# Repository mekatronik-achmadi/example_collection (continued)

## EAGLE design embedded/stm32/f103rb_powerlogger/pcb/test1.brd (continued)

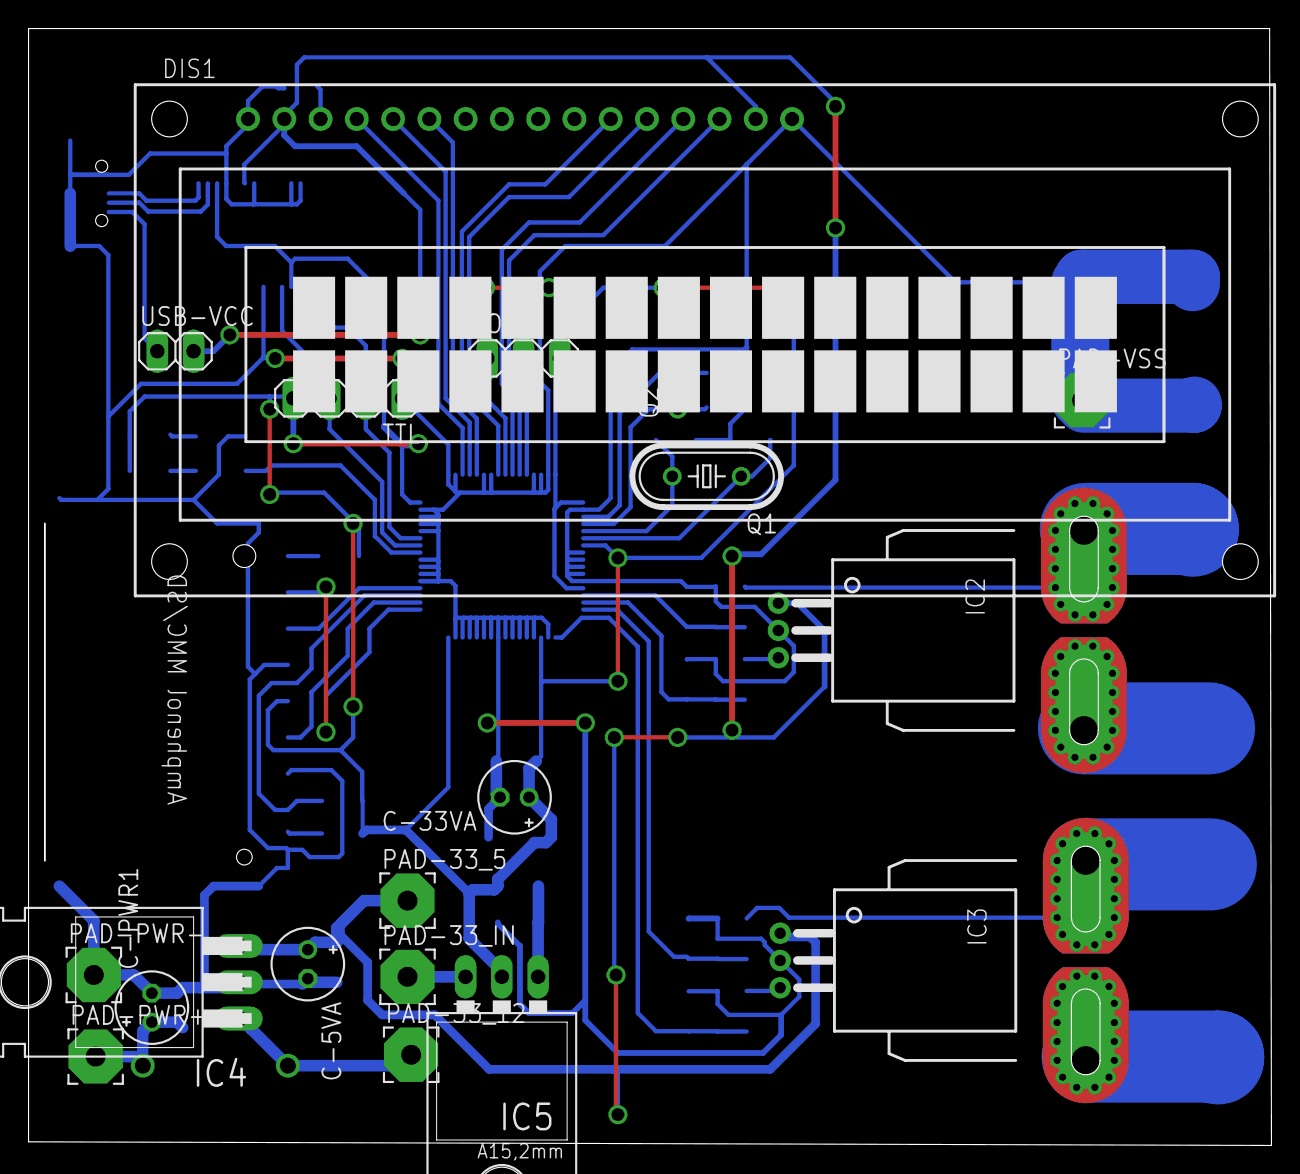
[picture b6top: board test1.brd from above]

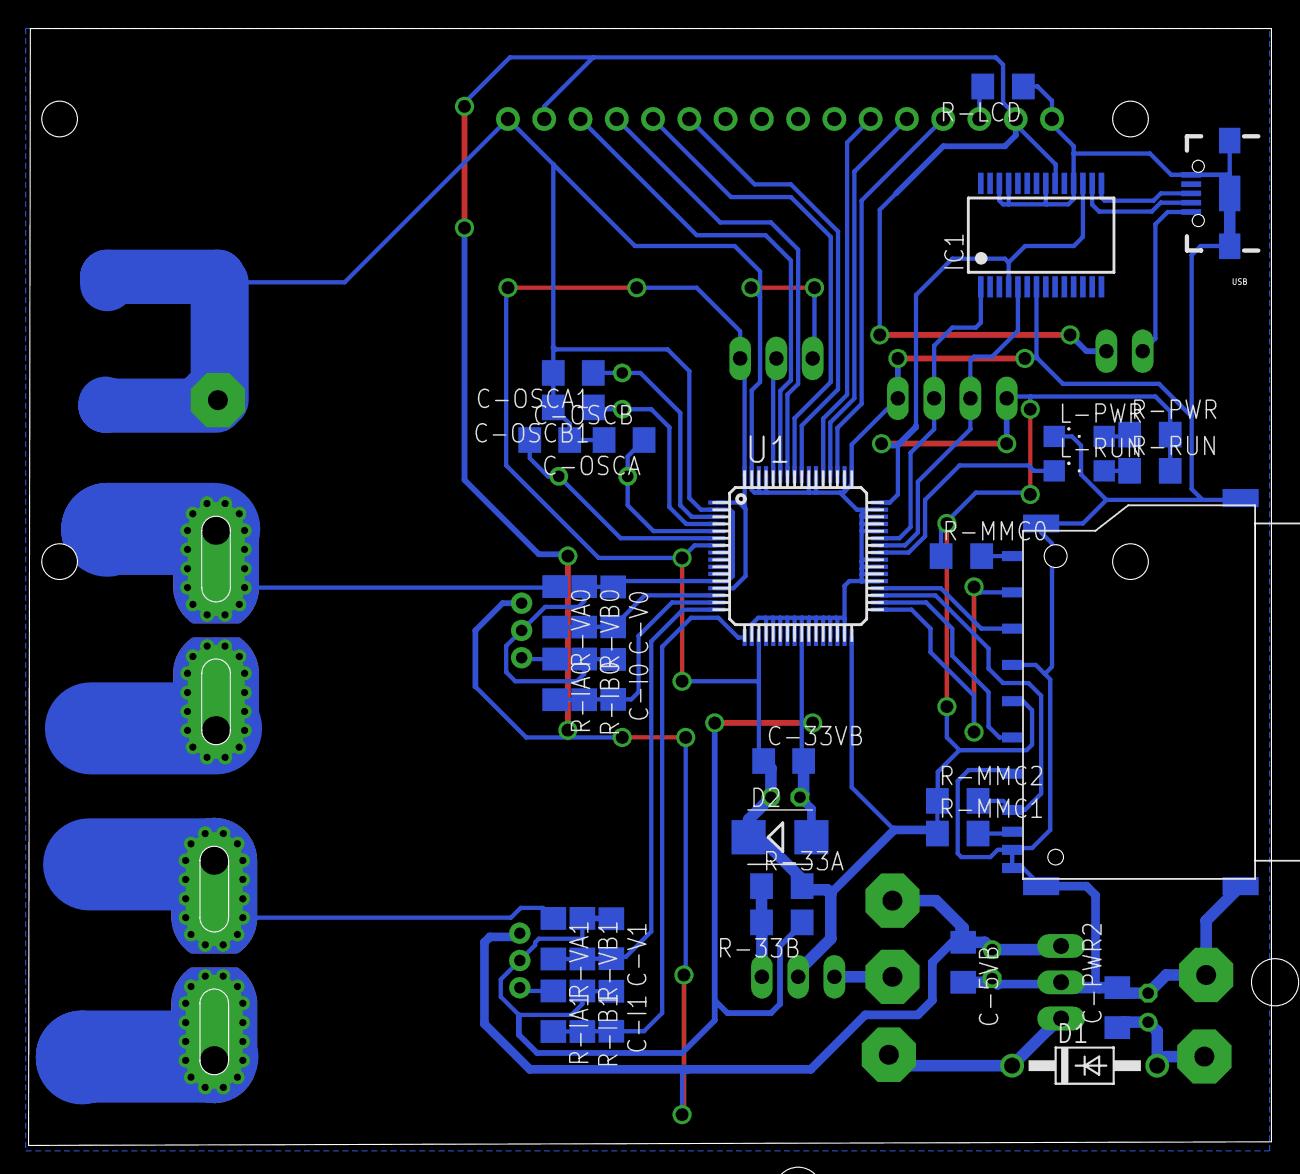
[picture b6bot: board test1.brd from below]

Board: 2 copper layers, 87.0 x 78.2 mm, 54 parts (35 on the bottom side), 42 nets.

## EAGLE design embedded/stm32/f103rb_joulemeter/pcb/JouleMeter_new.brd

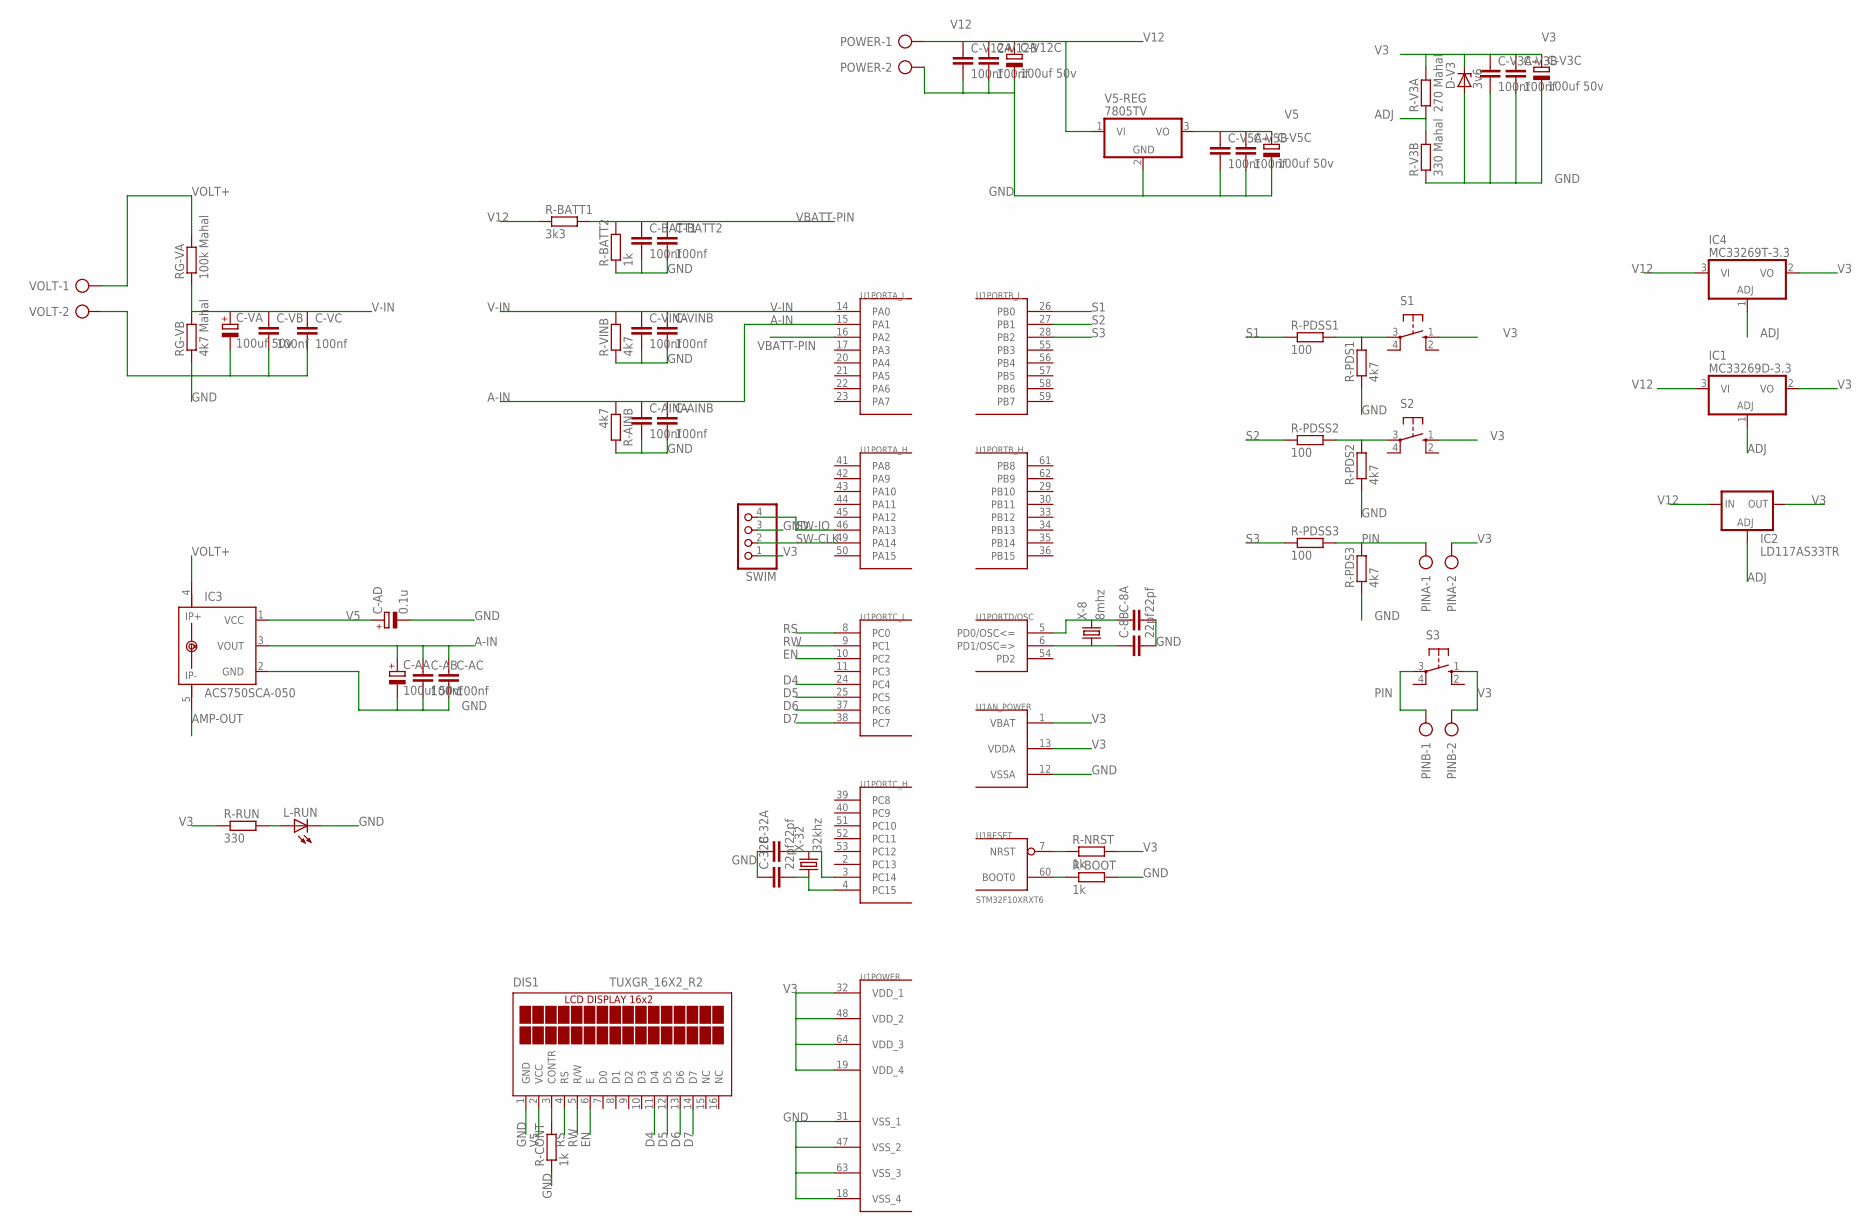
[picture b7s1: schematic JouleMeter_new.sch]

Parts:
C-8A, C-8B, C-32A, C-32B: 22pf; C025-024X044
C-AA: 100uf 50v; E2-5
C-AB: 100nf; C050-024X044
C-AC: 100nf; C050-024X044
C-AD: 0.1u; E2-5
C-AINA: 100nf; C050-024X044
C-AINB: 100nf; C050-024X044
C-BATT1, C-BATT2: 100nf; C050-024X044
C-V3A, C-V3B, C-V5A, C-V5B, C-V12A, C-V12B: 100nf; C050-024X044
C-V3C, C-V5C, C-V12C: 100uf 50v; E5-5
C-VA: 100uf 50v; E2-5
C-VB: 100nf; C050-024X044
C-VC: 100nf; C050-024X044
C-VINA: 100nf; C050-024X044
C-VINB: 100nf; C050-024X044
D-V3: 3v6; ZDIO-7.5
DIS1: TUXGR_16X2_R2
IC1: MC33269D-3.3; DPACK
IC2: LD117AS33TR; SOT223
IC3: ACS750SCA-050; ACS75050
IC4: MC33269T-3.3; TO220V
L-RUN: LED3MM
PINA: AK300/2
PINB: AK300/2
POWER: AK300/2
R-AINB: 4k7; 0204/7
R-BATT1: 3k3; 0204/7
R-BATT2: 1k; 0204/7
R-BOOT: 1k; 0204/7
R-CONT: 1k; 0204/7
R-NRST: 1k; 0204/7
R-PDS1, R-PDS2, R-PDS3: 4k7; 0204/7
R-PDSS1, R-PDSS2, R-PDSS3: 100; 0204/7
R-RUN: 330; 0204/7
R-V3A: 270 Mahal; 0204/7
R-V3B: 330 Mahal; 0204/7
R-VINB: 4k7; 0204/7
RG-VA: 100k Mahal; 0204/7
RG-VB: 4k7 Mahal; 0204/7
S1, S2: 10-XX; B3F-10XX
S3: 40-XX; B3F-40XX
SWIM: PINHD-1X4; 1X04
U1: STM32F10XRXT6; TQFP64
V5-REG: 7805TV; TO220V
VOLT: AK300/2
X-8: 8mhz; HC49U-V
X-32: 32khz; TC26V

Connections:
A-IN: C-AA.+, C-AB.1, C-AC.1, C-AINA.1, C-AINB.1, IC3.3 (VOUT), R-AINB.1, U1.15 (PA1)
ADJ: IC1.1 (ADJ), IC2.1 (ADJ), IC4.1 (ADJ), R-V3A.1, R-V3B.2
AMP-OUT: IC3.5 (IP-)
D4: DIS1.11 (D4), U1.24 (PC4)
D5: DIS1.12 (D5), U1.25 (PC5)
D6: DIS1.13 (D6), U1.37 (PC6)
D7: DIS1.14 (D7), U1.38 (PC7)
EN: DIS1.6 (E), U1.10 (PC2)
GND: C-8A.2, C-8B.2, C-32A.1, C-32B.1, C-AA.-, C-AB.2, C-AC.2, C-AD.-, C-AINA.2, C-AINB.2, C-BATT1.2, C-BATT2.2, C-V3A.2, C-V3B.2, C-V3C.-, C-V5A.2, C-V5B.2, C-V5C.-, C-V12A.2, C-V12B.2, C-V12C.-, C-VA.-, C-VB.2, C-VC.2, C-VINA.2, C-VINB.2, D-V3.A, DIS1.1 (GND), IC3.2 (GND), L-RUN.K (C), POWER.2, R-AINB.2, R-BATT2.1, R-BOOT.2, R-CONT.1, R-PDS1.1, R-PDS2.1, R-PDS3.1, R-V3B.1, R-VINB.1, RG-VB.1, SWIM.3, U1.12 (VSSA), U1.18 (VSS_4), U1.31 (VSS_1), U1.47 (VSS_2), U1.63 (VSS_3), V5-REG.2 (GND), VOLT.2
unnamed: R-PDS1.2, R-PDSS1.2, S1.3
unnamed: R-PDS2.2, R-PDSS2.2, S2.3
unnamed: DIS1.3 (CONTR), R-CONT.2
unnamed: C-32B.2, U1.4 (PC15), X-32.1
unnamed: C-32A.2, U1.3 (PC14), X-32.2
unnamed: C-8B.1, U1.6 (PD1/OSC=>), X-8.1
unnamed: C-8A.1, U1.5 (PD0/OSC<=), X-8.2
unnamed: R-NRST.1, U1.7 (NRST)
unnamed: R-BOOT.1, U1.60 (BOOT0)
unnamed: L-RUN.A, R-RUN.2
PIN: PINA.1, PINB.1, R-PDS3.2, R-PDSS3.2, S3.3
RS: DIS1.4 (RS), U1.8 (PC0)
RW: DIS1.5 (R/W), U1.9 (PC1)
S1: R-PDSS1.1, U1.26 (PB0)
S2: R-PDSS2.1, U1.27 (PB1)
S3: R-PDSS3.1, U1.28 (PB2)
SW-CLK: SWIM.2, U1.49 (PA14)
SW-IO: SWIM.4, U1.46 (PA13)
V3: C-V3A.1, C-V3B.1, C-V3C.+, D-V3.C, IC1.2 (VO), IC2.4 (OUT), IC4.2 (VO), PINA.2, PINB.2, R-NRST.2, R-RUN.1, R-V3A.2, S1.1 (S), S2.1 (S), S3.1 (S), SWIM.1, U1.1 (VBAT), U1.13 (VDDA), U1.19 (VDD_4), U1.32 (VDD_1), U1.48 (VDD_2), U1.64 (VDD_3)
V5: C-AD.+, C-V5A.1, C-V5B.1, C-V5C.+, DIS1.2 (VCC), IC3.1 (VCC), V5-REG.3 (VO)
V12: C-V12A.1, C-V12B.1, C-V12C.+, IC1.3 (VI), IC2.3 (IN), IC4.3 (VI), POWER.1, R-BATT1.1, V5-REG.1 (VI)
V-IN: C-VA.+, C-VB.1, C-VC.1, C-VINA.1, C-VINB.1, R-VINB.2, RG-VA.1, RG-VB.2, U1.14 (PA0)
VBATT-PIN: C-BATT1.1, C-BATT2.1, R-BATT1.2, R-BATT2.2, U1.16 (PA2)
VOLT+: IC3.4 (IP+), RG-VA.2, VOLT.1

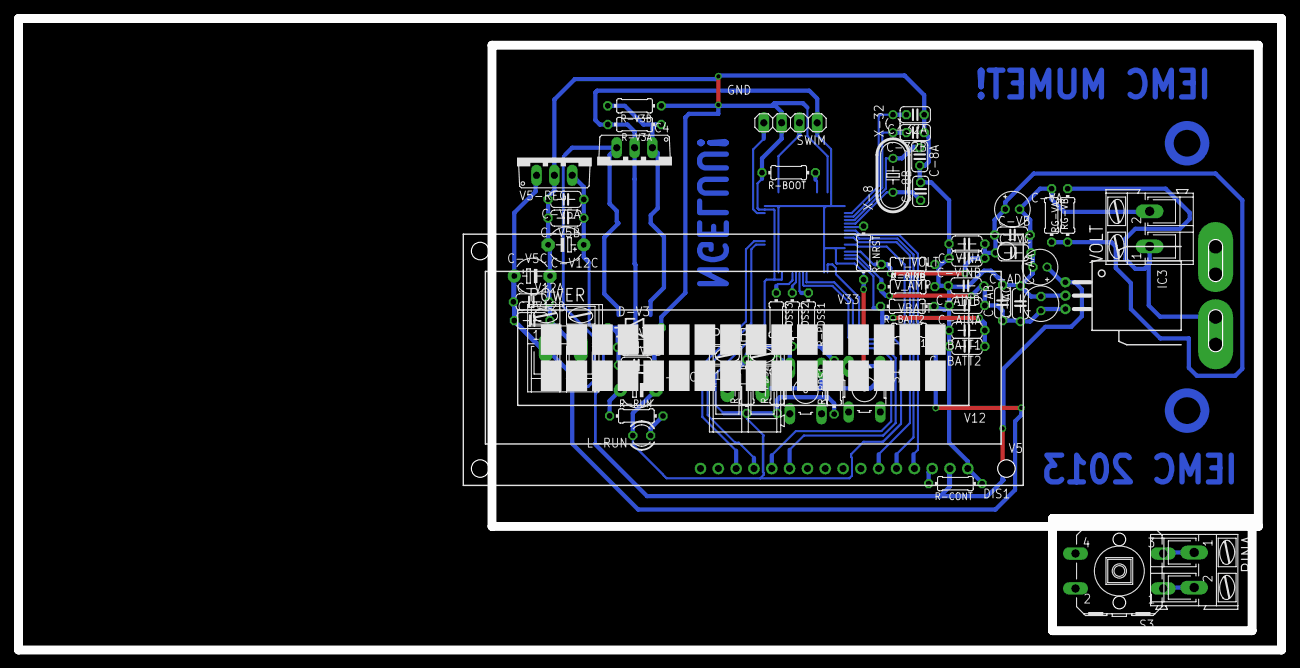
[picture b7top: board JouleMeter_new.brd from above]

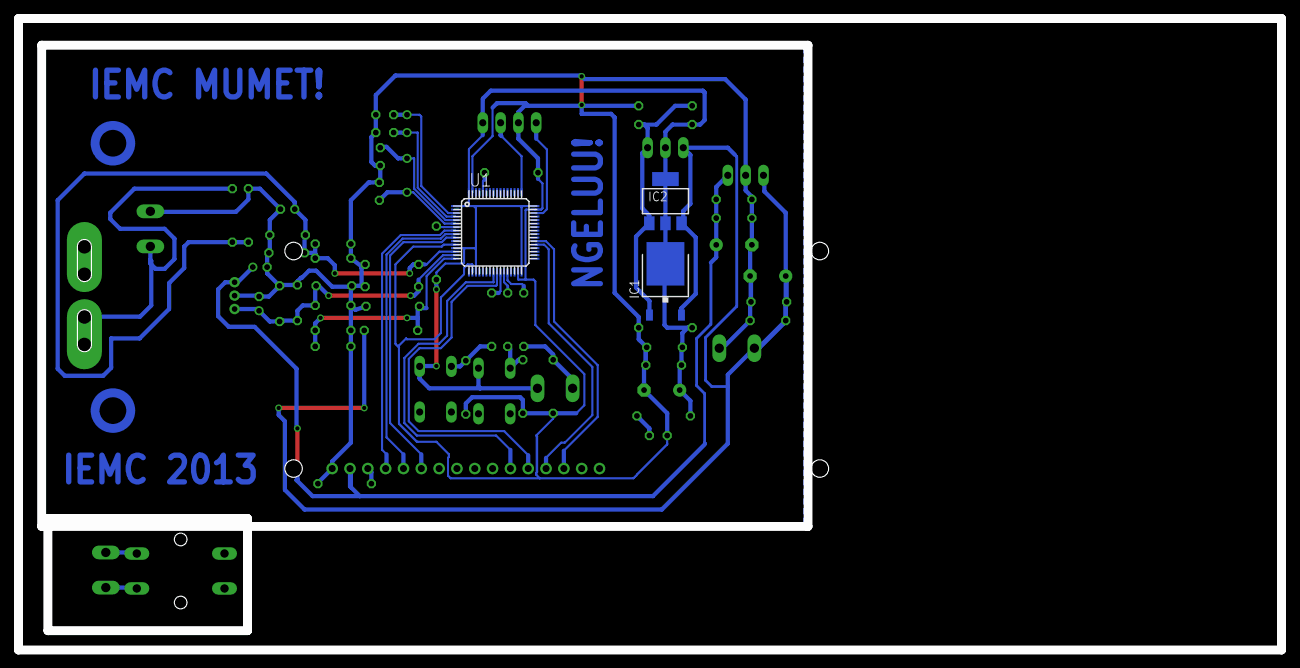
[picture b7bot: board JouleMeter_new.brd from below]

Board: 2 copper layers, 180.0 x 90.0 mm, 63 parts (3 on the bottom side), 32 nets.

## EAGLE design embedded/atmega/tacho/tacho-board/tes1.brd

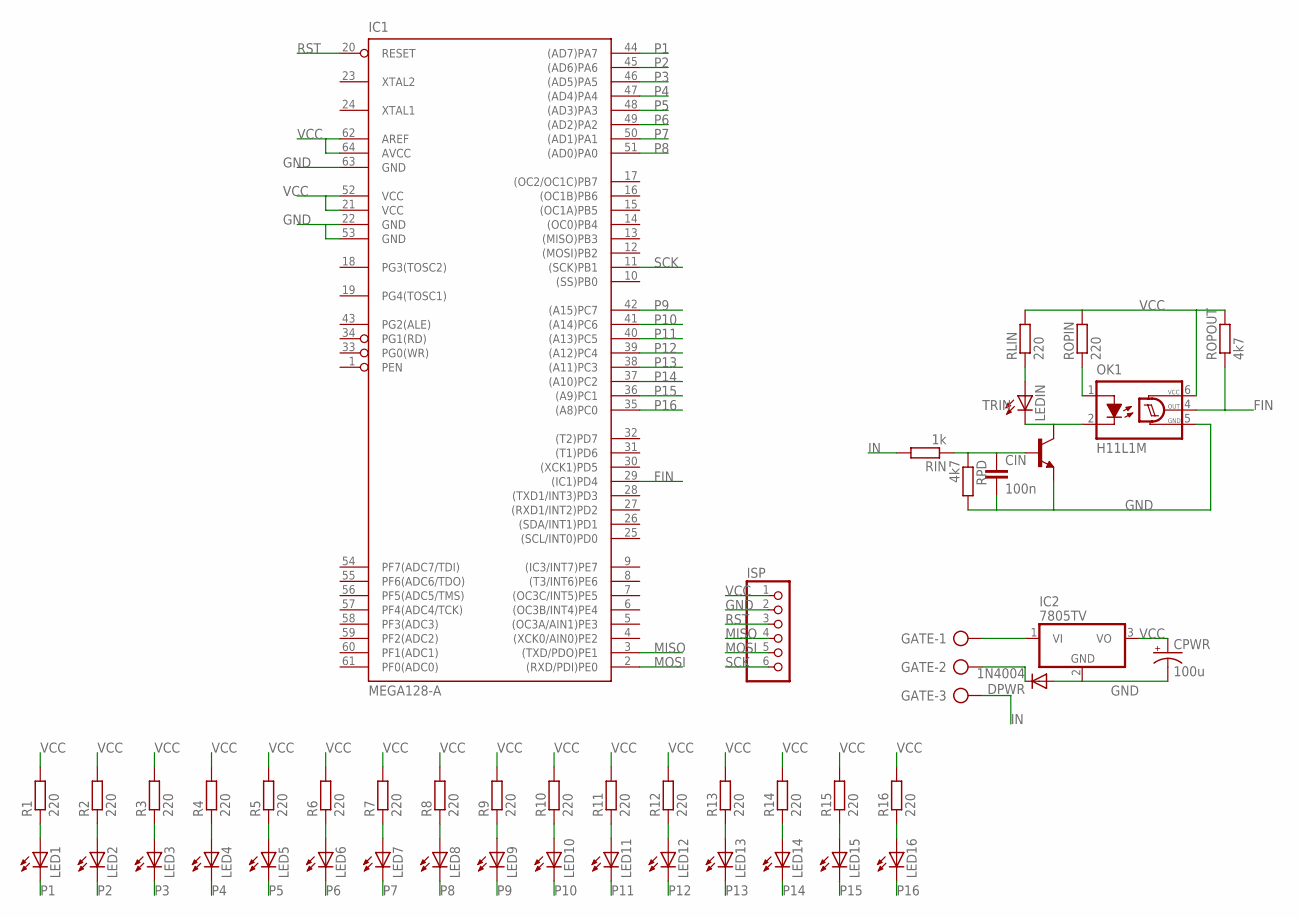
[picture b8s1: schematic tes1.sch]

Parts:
CIN: 100n; C050-024X044
CPWR: 100u; E2-5
DPWR: 1N4004; DO41-10
GATE: AK300/3
IC1: MEGA128-A; TQFP64
IC2: 7805TV; TO220V
ISP: PINHD-1X6; 1X06
LED1, LED2, LED3, LED4, LED5, LED6, LED7, LED8, LED9, LED10, LED11, LED12, LED13, LED14, LED15, LED16: LED3MM
LEDIN: LED3MM
OK1: H11L1M; DIL06
R1, R2, R3, R4, R5, R6, R7, R8, R9, R10, R11, R12, R13, R14, R15, R16: 220; 0204/7
RIN: 1k; 0204/7
RLIN: 220; 0204/7
ROPIN: 220; 0204/7
ROPOUT: 4k7; 0204/7
RPD: 4k7; 0204/7
TRIN: -NPN-TO92-EBC; TO92-EBC

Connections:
FIN: IC1.29 ((IC1)PD4), OK1.4 (OUT), ROPOUT.1
GND: CIN.2, CPWR.-, DPWR.A, IC1.22 (GND), IC1.53 (GND), IC1.63 (GND), IC2.2 (GND), ISP.2, OK1.5 (GND), RPD.2, TRIN.E
IN: GATE.3, RIN.2
MISO: IC1.3 ((TXD/PDO)PE1), ISP.4
MOSI: IC1.2 ((RXD/PDI)PE0), ISP.5
unnamed: LED2.A, R2.1
unnamed: LED3.A, R3.1
unnamed: LED1.A, R1.1
unnamed: LED4.A, R4.1
unnamed: LED5.A, R5.1
unnamed: LED6.A, R6.1
unnamed: LED7.A, R7.1
unnamed: LED8.A, R8.1
unnamed: LED9.A, R9.1
unnamed: LED10.A, R10.1
unnamed: LED11.A, R11.1
unnamed: LED12.A, R12.1
unnamed: LED13.A, R13.1
unnamed: LED14.A, R14.1
unnamed: LED15.A, R15.1
unnamed: LED16.A, R16.1
unnamed: DPWR.C, GATE.2
unnamed: GATE.1, IC2.1 (VI)
unnamed: CIN.1, RIN.1, RPD.1, TRIN.B
unnamed: LEDIN.K (C), OK1.2 (C), TRIN.C
unnamed: OK1.1 (A), ROPIN.1
unnamed: LEDIN.A, RLIN.1
P1: IC1.44 ((AD7)PA7), LED1.K (C)
P2: IC1.45 ((AD6)PA6), LED2.K (C)
P3: IC1.46 ((AD5)PA5), LED3.K (C)
P4: IC1.47 ((AD4)PA4), LED4.K (C)
P5: IC1.48 ((AD3)PA3), LED5.K (C)
P6: IC1.49 ((AD2)PA2), LED6.K (C)
P7: IC1.50 ((AD1)PA1), LED7.K (C)
P8: IC1.51 ((AD0)PA0), LED8.K (C)
P9: IC1.42 ((A15)PC7), LED9.K (C)
P10: IC1.41 ((A14)PC6), LED10.K (C)
P11: IC1.40 ((A13)PC5), LED11.K (C)
P12: IC1.39 ((A12)PC4), LED12.K (C)
P13: IC1.38 ((A11)PC3), LED13.K (C)
P14: IC1.37 ((A10)PC2), LED14.K (C)
P15: IC1.36 ((A9)PC1), LED15.K (C)
P16: IC1.35 ((A8)PC0), LED16.K (C)
RST: IC1.20 (RESET), ISP.3
SCK: IC1.11 ((SCK)PB1), ISP.6
VCC: CPWR.+, IC1.21 (VCC), IC1.52 (VCC), IC1.62 (AREF), IC1.64 (AVCC), IC2.3 (VO), ISP.1, OK1.6 (VCC), R1.2, R2.2, R3.2, R4.2, R5.2, R6.2, R7.2, R8.2, R9.2, R10.2, R11.2, R12.2, R13.2, R14.2, R15.2, R16.2, RLIN.2, ROPIN.2, ROPOUT.2

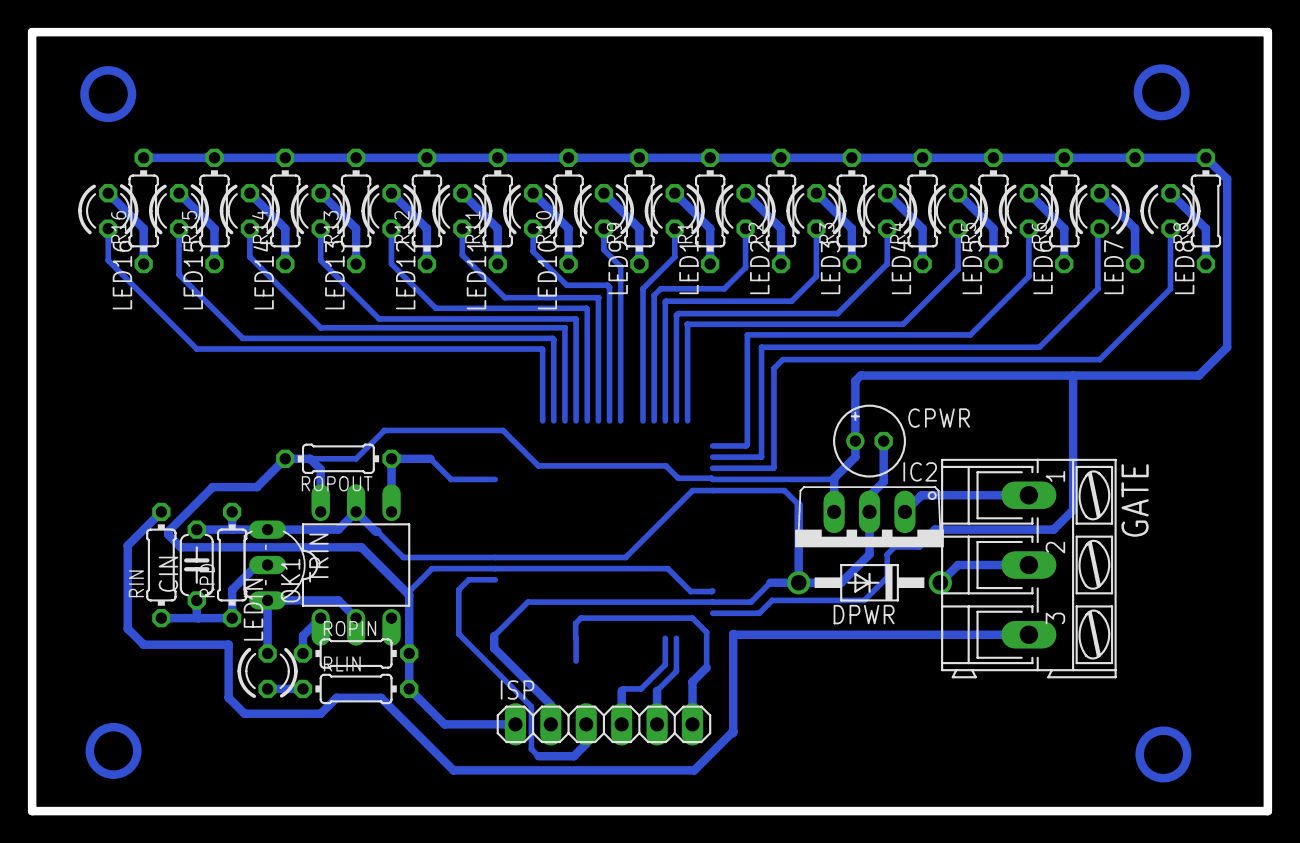
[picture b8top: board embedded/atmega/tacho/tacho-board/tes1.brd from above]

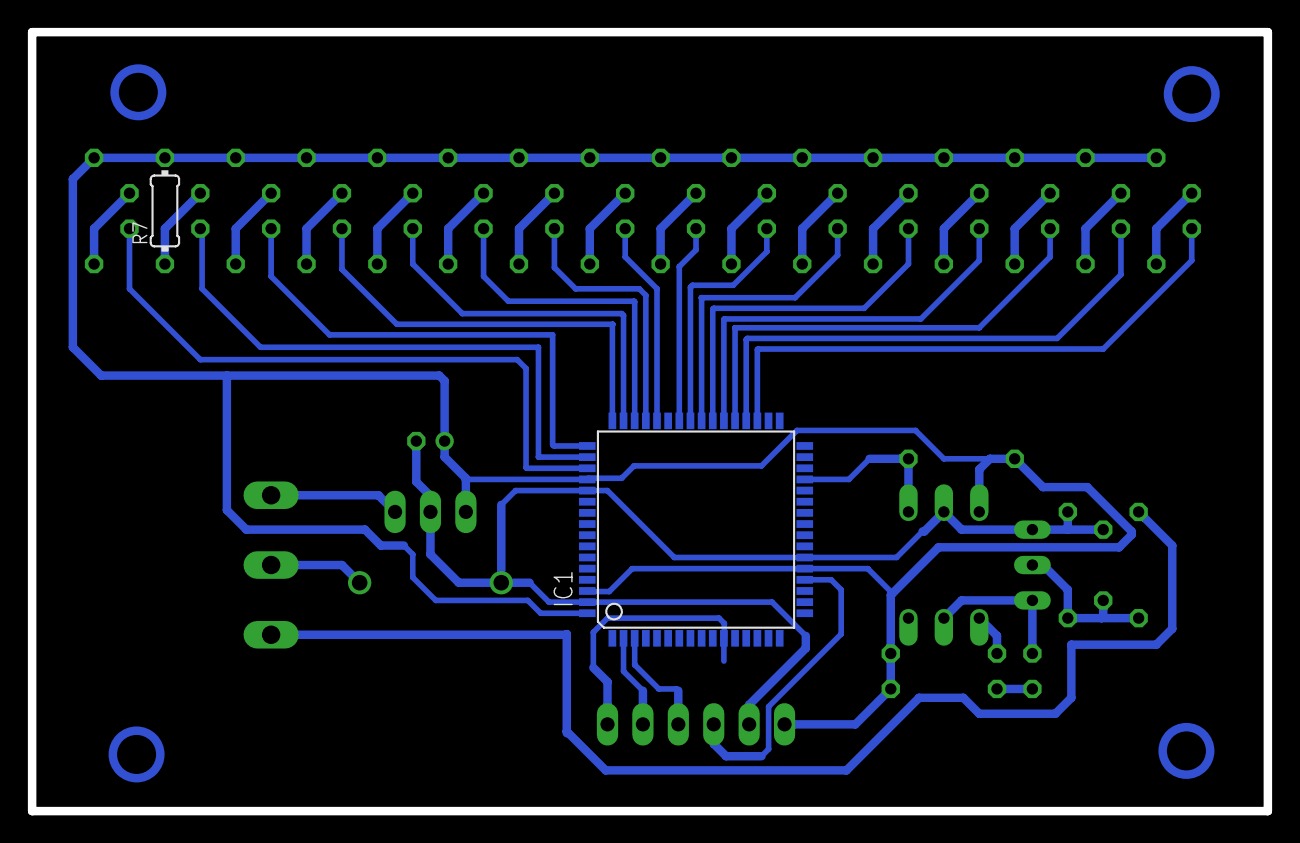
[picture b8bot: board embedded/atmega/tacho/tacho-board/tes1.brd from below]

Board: 2 copper layers, 88.6 x 55.9 mm, 47 parts (2 on the bottom side), 46 nets.

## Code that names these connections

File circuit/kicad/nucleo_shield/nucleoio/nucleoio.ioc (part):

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Mcu.Name=STM32F401R(D-E)Tx
Mcu.Package=LQFP64
Mcu.UserName=STM32F401RETx
PA10.Mode=Asynchronous
PA10.Signal=USART1_RX
PA13.GPIOParameters=GPIO_Label
PA13.GPIO_Label=TMS
PA13.Mode=Serial_Wire
PA13.Signal=SYS_JTMS-SWDIO
PA14.GPIOParameters=GPIO_Label
PA14.GPIO_Label=TCK
PA14.Mode=Serial_Wire
PA14.Signal=SYS_JTCK-SWCLK
PA15.Mode=NSS_Signal_Hard_Output
PA15.Signal=SPI3_NSS
PA2.GPIOParameters=GPIO_Speed,GPIO_PuPd,GPIO_Label,GPIO_Mode
PA2.GPIO_Label=USART_TX
PA2.GPIO_Mode=GPIO_MODE_AF_PP
PA2.GPIO_PuPd=GPIO_NOPULL
PA2.GPIO_Speed=GPIO_SPEED_FREQ_LOW
PA2.Mode=Asynchronous
PA2.Signal=USART2_TX
PA3.GPIOParameters=GPIO_Speed,GPIO_PuPd,GPIO_Label,GPIO_Mode
PA3.GPIO_Label=USART_RX
PA3.GPIO_Mode=GPIO_MODE_AF_PP
PA3.GPIO_PuPd=GPIO_NOPULL
PA3.GPIO_Speed=GPIO_SPEED_FREQ_LOW
PA3.Mode=Asynchronous
PA3.Signal=USART2_RX
PA5.GPIOParameters=GPIO_Speed,GPIO_PuPd,GPIO_Label,GPIO_Mode
PA5.GPIO_Label=LD2 [Green Led]
PA5.GPIO_Mode=GPIO_MODE_OUTPUT_PP
PA5.GPIO_PuPd=GPIO_NOPULL
PA5.GPIO_Speed=GPIO_SPEED_FREQ_LOW
PA5.Signal=GPIO_Output
PA9.Mode=Asynchronous
PA9.Signal=USART1_TX
PB2.Signal=GPIO_Input
PB3.GPIOParameters=GPIO_Label
PB3.GPIO_Label=SWO
PB3.Signal=SYS_JTDO-SWO
PC10.Mode=Full_Duplex_Master
PC10.Signal=SPI3_SCK
PC11.Mode=Full_Duplex_Master
PC11.Signal=SPI3_MISO
PC12.Mode=Full_Duplex_Master
PC12.Signal=SPI3_MOSI
PC13-ANTI_TAMP.GPIOParameters=GPIO_PuPd,GPIO_Label,GPIO_ModeDefaultEXTI
PC13-ANTI_TAMP.GPIO_Label=B1 [Blue PushButton]
PC13-ANTI_TAMP.GPIO_ModeDefaultEXTI=GPIO_MODE_IT_FALLING
PC13-ANTI_TAMP.GPIO_PuPd=GPIO_NOPULL
PC13-ANTI_TAMP.Signal=GPXTI13
PC14-OSC32_IN.Mode=LSE-External-Oscillator
PC14-OSC32_IN.Signal=RCC_OSC32_IN
PC15-OSC32_OUT.Mode=LSE-External-Oscillator
PC15-OSC32_OUT.Signal=RCC_OSC32_OUT
PH0\ -\ OSC_IN.Mode=HSE-External-Clock-Source
PH0\ -\ OSC_IN.Signal=RCC_OSC_IN
PH1\ -\ OSC_OUT.Mode=HSE-External-Clock-Source
PH1\ -\ OSC_OUT.Signal=RCC_OSC_OUT
RCC.HSE_VALUE=8000000
RCC.SYSCLKFreq_VALUE=84000000
RCC.SYSCLKSource=RCC_SYSCLKSOURCE_PLLCLK
board=NUCLEO-F401RE
boardIOC=true

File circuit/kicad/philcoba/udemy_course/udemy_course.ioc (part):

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Mcu.Name=STM32F103C(8-B)Tx
Mcu.Package=LQFP48
Mcu.UserName=STM32F103C8Tx
PA11.Mode=Device
PA11.Signal=USB_DM
PA12.Mode=Device
PA12.Signal=USB_DP
PA13.Mode=Serial_Wire
PA13.Signal=SYS_JTMS-SWDIO
PA14.Mode=Serial_Wire
PA14.Signal=SYS_JTCK-SWCLK
PB10.Mode=I2C
PB10.Signal=I2C2_SCL
PB11.Mode=I2C
PB11.Signal=I2C2_SDA
PB6.Mode=Asynchronous
PB6.Signal=USART1_TX
PB7.Mode=Asynchronous
PB7.Signal=USART1_RX
PC13-TAMPER-RTC.Signal=GPIO_Output
PD0-OSC_IN.Mode=HSE-External-Oscillator
PD0-OSC_IN.Signal=RCC_OSC_IN
PD1-OSC_OUT.Mode=HSE-External-Oscillator
PD1-OSC_OUT.Signal=RCC_OSC_OUT
RCC.SYSCLKFreq_VALUE=48000000
RCC.SYSCLKSource=RCC_SYSCLKSOURCE_PLLCLK
board=custom

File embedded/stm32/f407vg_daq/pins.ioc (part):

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Mcu.Name=STM32F407V(E-G)Tx
Mcu.Package=LQFP100
PA10.Mode=Asynchronous
PA10.Signal=USART1_RX
PA9.Mode=Asynchronous
PA9.Signal=USART1_TX
PB12.Mode=Full-Duplex-Master_With-NSS
PB12.Signal=SPI2_NSS
PB13.Mode=Full-Duplex-Master_With-NSS
PB13.Signal=SPI2_SCK
PB8.Mode=I2C
PB8.Signal=I2C1_SCL
PB9.Mode=I2C
PB9.Signal=I2C1_SDA
PC2.Mode=Full-Duplex-Master_With-NSS
PC2.Signal=SPI2_MISO
PC3.Mode=Full-Duplex-Master_With-NSS
PC3.Signal=SPI2_MOSI
PE0.GPIOParameters=GPIO_Label
PE0.GPIO_Label=ALCD_RS
PE0.Signal=GPIO_Output
PE1.GPIOParameters=GPIO_Label
PE1.GPIO_Label=ALCD_EN
PE1.Signal=GPIO_Output
PE4.GPIOParameters=GPIO_Label
PE4.GPIO_Label=ALCD_D4
PE4.Signal=GPIO_Output
PE5.GPIOParameters=GPIO_Label
PE5.GPIO_Label=ALCD_D5
PE5.Signal=GPIO_Output
PE6.GPIOParameters=GPIO_Label
PE6.GPIO_Label=ALCD_D6
PE6.Signal=GPIO_Output
PE7.GPIOParameters=GPIO_Label
PE7.GPIO_Label=ALCD_D7
PE7.Signal=GPIO_Output

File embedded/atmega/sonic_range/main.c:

/*
Project:	pak_den
Board:		uno
MCU:		16MHzatmega328
FRENQUENCY:	16000000

Created using QtCreator
*/

#include <avr/io.h>
#include <avr/interrupt.h>
#include <util/delay.h>
#include <inttypes.h>
#include <stdio.h>
#include <stdlib.h>
#include <avr/eeprom.h>
#include <avr/pgmspace.h>

////////////////////////////////////////////////////////////

// beberapa pre-define

#define trig_pin    3 //PD3
#define echo_pin    2 //PD2 - INT0
#define led_pin     5 //PB5

#define DELAY_MS    100
#define baud_rate   9600

////////////////////////////////////////////////////////////

// Implementasi fungsi tunda
void delay_ms(unsigned int time){
    unsigned int i;

    for(i=0;i<time;i++){
        _delay_ms(1);
    };
    return;
}

void delay_us(unsigned int time){
    unsigned int i;

    for(i=0;i<time;i++){
        _delay_us(1);
    };
    return;
}

////////////////////////////////////////////////////////////

// Implementasi standar I/O data ASCII
static int uart_putchar(char ch,FILE*stream)
{
    if(ch=='\n'){uart_putchar('\r',stream);}
    while ((UCSR0A & (1 << UDRE0)) == 0) {};
    UDR0=ch;
    return 0;
}

static FILE uart_stdout=FDEV_SETUP_STREAM(uart_putchar,NULL,_FDEV_SETUP_WRITE);

////////////////////////////////////////////////////////////

// inisialisasi variable global
volatile unsigned int tick, cacah;

////////////////////////////////////////////////////////////

// referensi fungsi-fungsi global

static void tim0_active(unsigned char stt){
    // timer clock senilai 1/8 dari clock utama
    if(stt==1){
        TCCR0B|=(1<<CS00);
    }
    else if(stt==0){
        TCCR0B&=~(1<<CS00);
    }
}

static void sensor_ukur(void){
    tick = 0;
    cacah = 0;

    // kirim sinyal trigger
    PORTD |= (1<< trig_pin);
    delay_us(10);
    PORTD &= ~(1<< trig_pin);
    delay_ms(100);

    // aktifkan Timer 0 untuk pencacahan
    tim0_active(1);
}

////////////////////////////////////////////////////////////

int main()
{

    // pengaturan LED
    // Arduino : pin Digital 5
    // ATMega  : port B5

    // diatur sebagai output
    DDRB |= 1<< led_pin;

    // nilainya low (led mati)
    PORTB &= ~(1<< led_pin);
////////////////////////////////////////////////////////////
    // inisialisasi fitur komunikasi serial UART (Universal Asychronous Rx Tx)

    // aktifasi register serial (1 bit)
    UCSR0B|=1<<TXEN0;

    // pengaturan baudrate atau kecepatan (16 bit)
    UBRR0H=(((F_CPU / (baud_rate * 16UL))) - 1)>>8;
    UBRR0L=(((F_CPU / (baud_rate * 16UL))) - 1);

    // pengaturan mode 8n1 (8 bit)
    UCSR0C|=(1<<UCSZ01)|(1<<UCSZ00);

    // retarget fungsi printf()
    stdout=&uart_stdout;
////////////////////////////////////////////////////////////
    // aktifasi pin untuk Trigger HC-SR04
    // Arduino pin : Digital 3
    // ATmega pin : port D3

    // diatur sebagai output
    DDRD |= 1<< trig_pin;

    // nilai awal Low
    PORTD &= ~(1<< trig_pin);

////////////////////////////////////////////////////////////
    // aktifasi pin untuk Echo HC-SR04
    // Arduino pin : Digital 2
    // ATMega pin : pin D2
    // Interrupt : INT0

    // diatur sebagai input
    DDRD &= ~(1<< echo_pin);

    // nilai di pull-up
    PORTD |= 1<< echo_pin;

    // Interrtupt pada Falling-Edge
    EICRA |= 1<<ISC01;

    // Aktifasi interrupt INT0
    EIMSK |= 1 << INT0;

////////////////////////////////////////////////////////////
    // inisialisasi Timer 0 untuk pencacah

    // aktifasi Timer Overflow interrupt
    TIMSK0 |=1<<TOIE0;

    // deaktifasi awal
    tim0_active(0);

////////////////////////////////////////////////////////////

    // aktifkan semua interrupt
    sei();

////////////////////////////////////////////////////////////

    while (1)
    {

        // mulai ukur nilai
        sensor_ukur();
        delay_ms(100);

        // kirim nilai register lewat serial
        printf("%i\n\r",cacah);

        // tunda untuk pengukuran selanjutnya
        delay_ms(500);
    }

}

////////////////////////////////////////////////////////////

// fungsi-fungsi interrupt handler

// interrupt untuk IC Timer Overflow
ISR(TIMER0_OVF_vect){
    tick++;
}

// interrupt untuk INT 0
ISR(INT0_vect){
    tim0_active(0);

    if((tick<=0) || (tick>250)){
        cacah = 0;
    }
    else{
        cacah = tick;
    }
}

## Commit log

2021-11-26 first Flutter
2021-11-26 first atmega
2021-11-26 more atmega
2021-11-26 first esp8266
2021-11-26 mqtt esp8266
2021-11-26 doorwatch esp8266
2021-11-26 phtdsmeter esp8266
2021-11-26 first rtos esp8266
2021-11-26 esp8266
2021-11-27 first stm32
2021-11-27 stm32
2021-11-27 m2560_las_orbit
2021-11-29 ta nya didin
2021-11-30 stm32 more examples
2021-12-15 f429disc examples
2021-12-15 c webkit
2021-12-15 new circuit
2021-12-15 mega16_training
2021-12-15 wxserial
2021-12-16 more kicad examples
2021-12-16 gtk examples
2021-12-16 java examples
2021-12-16 octave examples
2021-12-16 more examples
2021-12-16 python academic examples
2021-12-16 qt examples
2021-12-16 stm32 chibios examples
2021-12-16 finish selecting examples
2021-12-16 clean-up unnecessary non text files
2021-12-16 some stm32 examples
2021-12-16 esp32 examples
2022-01-05 update stm32 sensor example
2022-01-11 Mini PV
2022-01-11 PCB Mini PV
2022-01-16 esp32 blink
2022-01-16 esp8266 example
2022-02-18 papank PCB
2022-02-18 esp32 dsp example
2022-02-18 ESP DSP FFT is weird
2022-02-19 esp32 mic fft doxygen
2022-02-19 esp32 mic fft doxygen dark
2022-02-20 doxygen
2022-02-25 KiCAD tutorial
2022-02-26 SMD Tutorial
2022-03-04 wxWidget CPP
2022-03-14 btserial
2022-03-14 btserial_keypad
2022-03-14 btspp
2022-03-14 btspp OLED
2022-03-14 btspp string handle
2022-03-14 bt spp text handler
2022-03-15 string/char handler error
2022-03-15 need handle sring more than 20
2022-03-15 string handle
2022-03-15 40 strings OK
2022-03-15 first demo
2022-03-15 Include PDF schematic
2022-03-24 coba js server
2022-04-09 stm32 driver
2022-05-21 pid example in python
2022-07-20 ESP32 IDF Arduino Example
2022-07-20 ESP OLED IDF
2022-07-20 ESP IDF
2022-07-20 ESP32 OLED IDF
2022-07-20 ESP32 IDF OLED
2022-07-20 ESP32 OLED Arduino
2022-07-20 ESP32 Arduino
2022-07-20 Typo
2022-07-20 Arduino sucks
2022-07-21 ESP32 Arduino compileable but LCD blank
2022-07-21 ESP32 Arduino OLED Example
2022-07-21 ESP32 Arduino OLED done
2022-09-08 ESP32 Audio Tester
2022-09-08 Schematic Done
2022-09-08 ESP32 Audio
2022-09-20 some examples
2022-10-02 ESP32 AP Webserver
2022-10-02 ESP32 Version
2022-10-02 ESP32 HTTPD
2022-12-27 KiCAD JLC Tutorial
2022-12-27 KiCAD JLC
2022-12-31 Serial Example
2022-12-31 WX serial
2022-12-31 Cross Serial Terminal wxWidget
2022-12-31 Cross Serial Terminal Qt
2022-12-31 Cross Serial Qt
2023-01-01 Cross Serial Gtk
2023-01-02 GTK is so weird
2023-01-02 GTK GUI Serial
2023-01-02 GTK is weird
2023-01-02 Readme Cross Serial
2023-01-03 Gtk has no input dialog like Qt or wxWidgets
2023-01-03 Port/Baudrate no Input Dialog
2023-01-03 Cross Serial Qt Update
2023-01-03 Some basic AVR example
2023-01-03 AVR Basic Example
2023-01-03 Basic AVR example
2023-01-06 CodeVisionAVR on Simulide
2023-01-15 OptoIsolate Example
2023-01-16 UVW BLDC Example
2023-01-16 Learn JLCPCB
2023-01-26 Migrate Eagle-KiCAD: FT232RL
2023-01-26 Migrate Eagle-KiCAD: USBASP
2023-01-26 Migrate Eagle-KiCAD
2023-03-23 Some Academic Python Tools
2023-03-23 Some Academic Python tool
2023-03-23 Some Academic Tool
2023-03-23 Some Academic Tools First Run OK
2023-03-23 Some Academic Python Tool OK
2023-03-24 STM32 board
2023-03-25 STM32PP
2023-03-25 STM32 PP
2023-04-14 STM32 UART Example
2023-05-10 JSON C
2023-05-11 C JSON Collections
2023-05-11 JSON C Library
2023-05-11 JSON C example
2023-05-13 Tes JSON
2023-05-15 Parse String without strtok
2023-05-15 Parse Text
2023-06-07 STM32 KiCAD Example from Phils-Lab
2023-06-25 Shield Nucleo
2023-06-25 Nucleo Shield
2023-07-09 Recursive Example
2023-07-09 Try on ESP8266
2023-07-09 SinC on ESP8266
2023-08-17 STM32 LQFP64 Minimum System
2023-08-17 Progress
2023-08-17 Coba Pesan
2023-08-17 Ordering
2023-08-18 Update PCB to be Smaller
2023-08-18 update PCB
2023-08-27 Update PCB LQFP64
2023-08-27 Gerber LQFP64
2023-08-27 Uodate LQFP64
2023-09-11 Gtkmm examples
2023-10-09 ESP12-F Module
2023-10-09 ESP12-F
2023-10-09 ESP12F
2023-10-09 ESP-12F
2023-10-09 Kuliah Sinyal Ngulang
2023-10-30 Trying LoRA
2023-10-30 Lora Sender Arduino
2023-10-30 LoRA Arduino Receiver
2023-10-30 Arduino LoRA OK
2023-11-06 STM32 Arduino LoRA
2023-11-06 LoRA STM32 seem disconnected
2023-11-06 STM32 Arduino LoRA not work
2023-11-06 LoRA Chibios Porting
2023-11-06 CHibiOS Lora
2023-11-07 Arduino STM32 LoRA
2023-11-07 STM32 BluePill Lora Failed
2023-11-07 LoRa STM32 to AVR OK
2023-11-07 Lora AVR to STM32 OK
2023-11-07 LoRA Sender only
2023-11-07 Incomplete Sending Data
2023-11-07 Its working as byte data
2023-11-07 Send data in bytes
2023-11-07 Start Working on STM32 LoRA receiver
2023-11-07 Start Working on Receiver
2023-11-07 LoRa CHibiOS
2023-11-07 LoRA receiver STM32
2023-11-09 LoRa STM32 Improvements
2023-11-09 LoRA example OK
2023-11-09 Number Sending
2023-11-09 LoRA Plot
2023-12-11 STM8 Blink
2023-12-11 STM8 Examples
2023-12-11 STM8 is simpler but harder
2023-12-18 wxWidget Serial Terminal
2024-01-15 Gtk Vala
2024-02-16 ESP32 Mic
2024-02-16 ESP32 Sound In
2024-02-16 ESP Sound
2024-02-17 Mic Failed
2024-02-17 SPH0645 All Zero
2024-02-17 SPH0645 No Work
2024-02-17 Plot Mic
2024-02-18 Sound Input esp8266
2024-02-18 ESP Sound In
2024-02-18 ESP8266 Mic
2024-02-18 SPH0645 Still Zero
2024-02-18 SPH0645 Pio not work
2024-02-19 Drop ESP8288 as too slow for I2S Mic
2024-02-19 Retry ESP8266 I2S Mic
2024-02-19 ESP8266 I2S Mic Not Work
2024-02-20 Rewiring
2024-02-20 I2S Mic all Zero
2024-02-20 Still Zero
2024-02-20 Its not zero but weird
2024-02-20 Move ESP32 Mic to PlatformIO
2024-02-20 ESP32 I2S work on IDF so far
2024-02-21 PlatformIO ESP32 Mic
2024-02-21 Mic ESP32
2024-02-21 ESP32 PIO
2024-02-21 PIO VSCode
2024-02-23 Serial Plot
2024-02-23 Python Serial Plot
2024-02-24 PlatformIO Notes
2024-02-26 PlatformIO Menu
2024-02-28 Use VSCode C_CPP
2024-02-29 PIO verbose
2024-03-02 VSCode Intellisense
2024-03-07 Notes
2024-03-09 Rust Example
2024-03-10 Rust Examples
2024-03-12 Rust Array
2024-03-13 Rust Thread
2024-03-14 Rust Note
2024-03-18 Qt Serial Terminal
2024-03-18 Old Serial Qt5
2024-03-19 FLTK Serial Failed
2024-03-19 FLTK Examples
2024-03-22 Some Updates
2024-03-22 GoLang example
2024-03-25 RustFMT examples
2024-03-27 C Pointer
2024-03-31 Drop FLTK Examples
2024-04-04 NodeJS example
2024-04-04 NodeJS HTML Half Failed
